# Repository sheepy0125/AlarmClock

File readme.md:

# Alarm Clock

An Alarm Clock created as a school project.

## Hardware (general)

Uses an Arduino Uno (`atmega328p`) as the processor to control:
- 6x 7-segment digits for hours, minutes, and seconds
- 1x character LCD
- 1x snooze button (key switch)
- 1x rotary encoder to adjust time and change other settings (as seen on the LCD)
- 1x piezo buzzer
- 1x real time clock

### Shift registers

Because the Uno only has ~19 available pins, I used serial-in parallel-out buffered shift registers to send one bit at a time and release 8 bits all at once. Each shift register typically needs 2 pins at minimum (one for serial in and one for clock), however, for the seven segment displays I cut that down to 1 per and 1 total for an amortized 7 pins in total where all shift registers share one clock pulse.

## Software

All software is written in Rust with [Rahix's Arduino HAL crate](https://github.com/rahix/avr-hal).

## Design

TODO!!!

## Progress

- [x] Design schematic (done: 2023-09-17)
- [x] Order parts
- [ ] Breadboard / POC (in progress)
- [ ] Design PCB
- [ ] Order PCB parts
- [ ] Finish software (in progress)
- [x] Construct case
- [ ] Integration

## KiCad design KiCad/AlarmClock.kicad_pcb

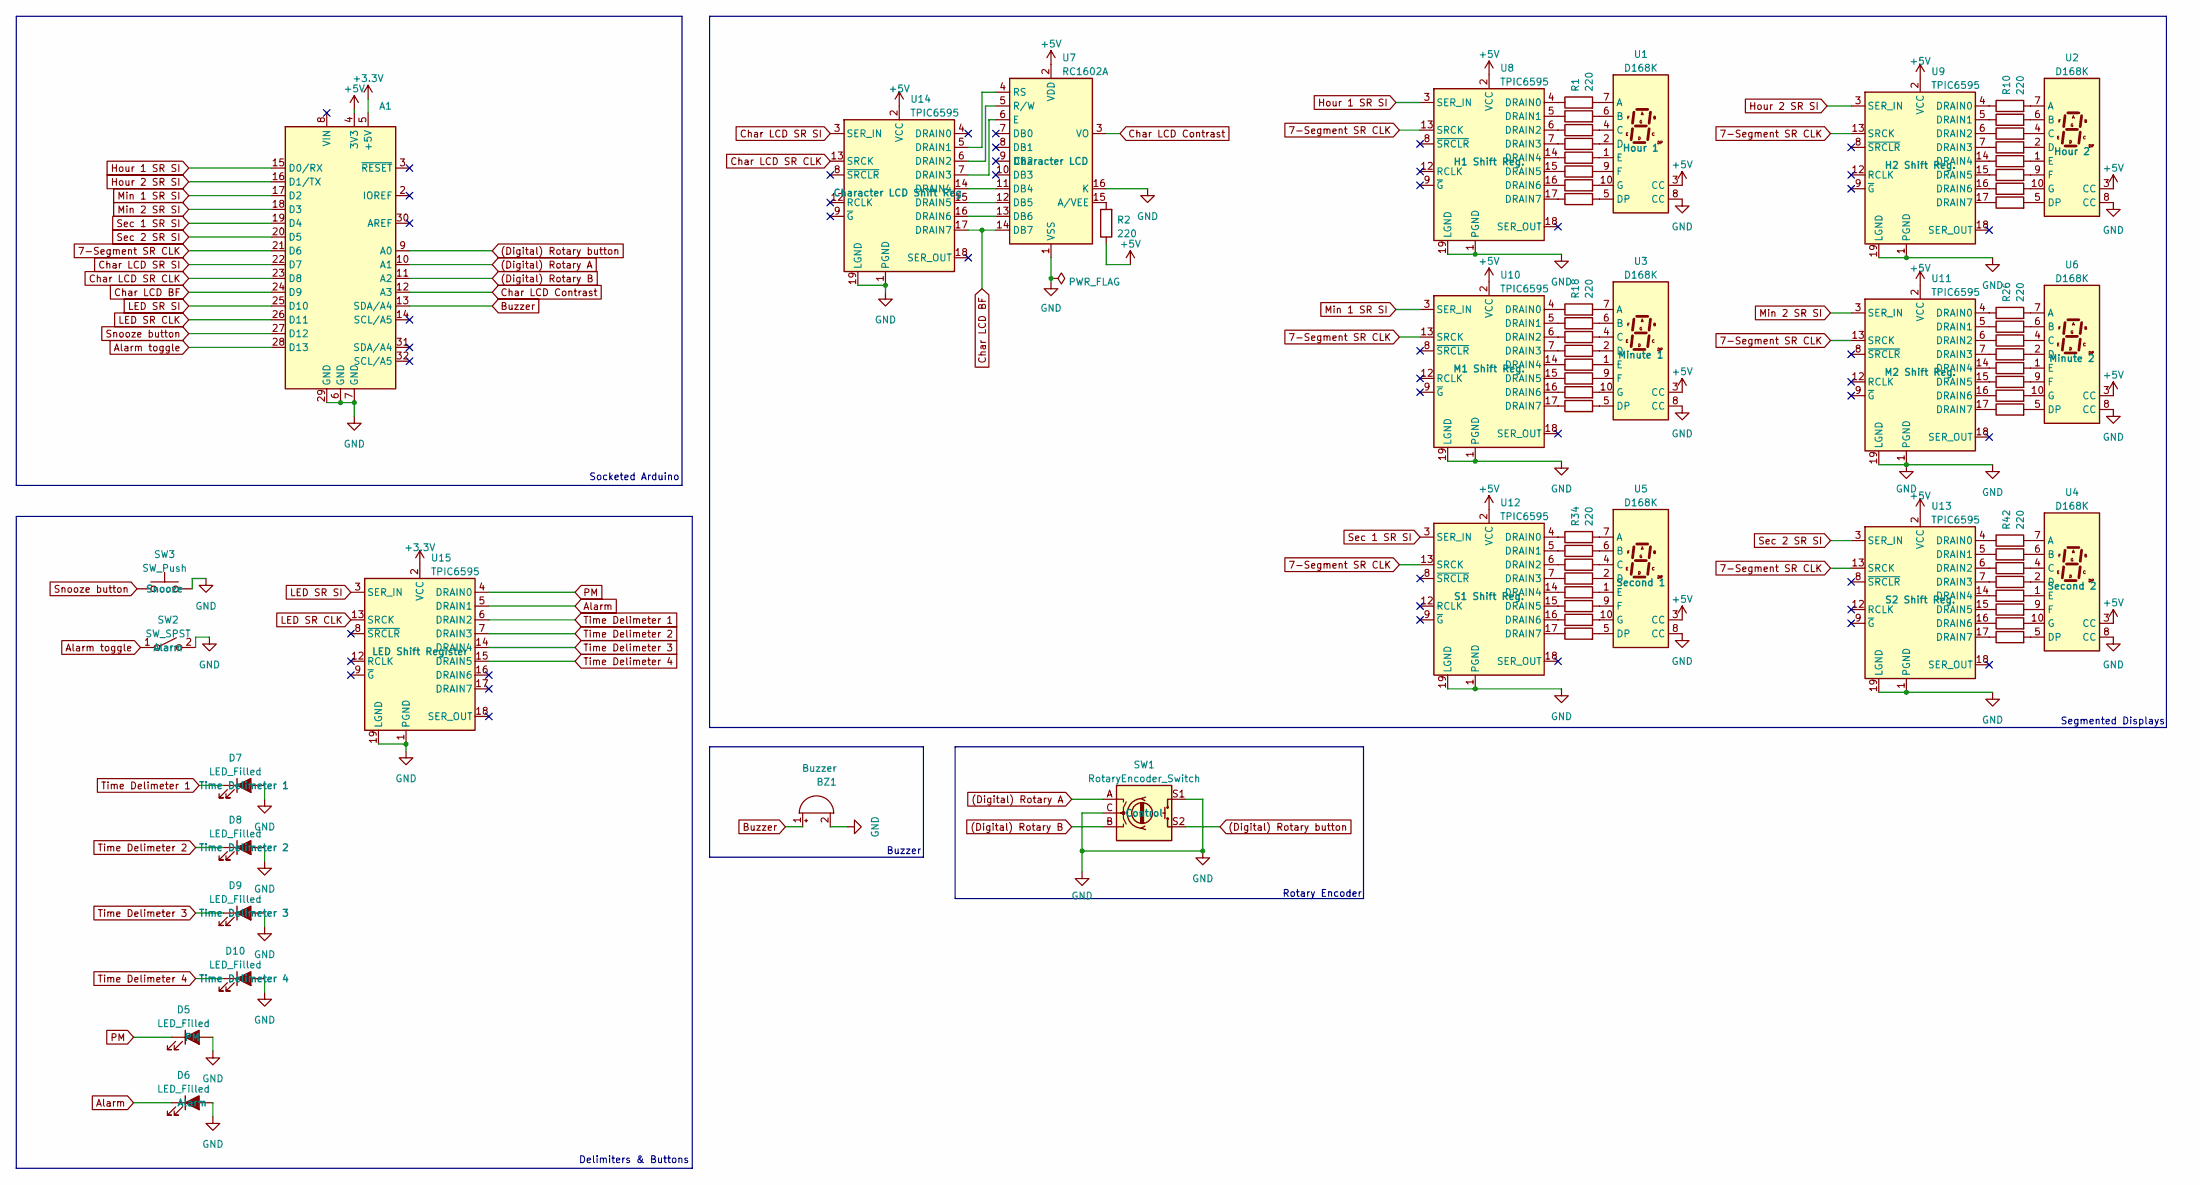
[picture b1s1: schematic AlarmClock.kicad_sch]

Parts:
A1: Arduino_UNO_R3; Arduino_UNO_R3_WithMountingHoles
BZ1: Buzzer; Buzzer_12x9.5RM7.6
D5, D6, D7, D8, D9, D10: LED_Filled; LED_D5.0mm
R1, R2, R3, R4, R5, R6, R7, R8, R9, R10, R11, R12, R13, R14, R15, R16, R17, R18, R19, R20, R21, R22, R23, R24, R25, R26, R27, R28, R29, R30, R31, R32, R33, R34, R35, R36, R37, R38, R39, R40, R41, R42, R43, R44, R45, R46, R47, R48, R49: 220; R_0402_1005Metric
SW1: RotaryEncoder_Switch; RotaryEncoder_Alps_EC11E-Switch_Vertical_H20mm
SW2: SW_SPST; SW_DIP_SPSTx01_Slide_6.7x4.1mm_W8.61mm_P2.54mm_LowProfile
SW3: SW_Push; SW_MX_1u
U1, U2, U3, U4, U5, U6: D168K; D1X8K
U7: RC1602A
U8, U9, U10, U11, U12, U13, U14, U15: TPIC6595; DIP-20_W7.62mm_Socket

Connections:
7-Segment SR CLK: A1.21 (D6), U8.13 (SRCK), U9.13 (SRCK), U10.13 (SRCK), U11.13 (SRCK), U12.13 (SRCK), U13.13 (SRCK)
(Digital) Rotary A: A1.10 (A1), SW1.A
(Digital) Rotary B: A1.11 (A2), SW1.B
(Digital) Rotary button: A1.9 (A0), SW1.S2
+3.3V: A1.5 (+5V), U15.2 (VCC)
Alarm: D6.1 (K), U15.5 (DRAIN1)
Alarm toggle: A1.28 (D13), SW2.1 (A)
Buzzer: A1.13 (SDA/A4), BZ1.1 (-)
Char LCD BF: A1.24 (D9), U7.14 (DB7), U14.17 (DRAIN7)
Char LCD Contrast: A1.12 (A3), U7.3 (VO)
Char LCD SR CLK: A1.23 (D8), U14.13 (SRCK)
Char LCD SR SI: A1.22 (D7), U14.3 (SER_IN)
GND: A1.6 (GND), A1.7 (GND), A1.29 (GND), BZ1.2 (+), D5.2 (A), D6.2 (A), D7.2 (A), D8.2 (A), D9.2 (A), D10.2 (A), SW1.C, SW1.S1, SW2.2 (B), SW3.2, U1.8 (CC), U2.8 (CC), U3.8 (CC), U4.8 (CC), U5.8 (CC), U6.8 (CC), U7.1 (VSS), U7.16 (K), U8.1 (PGND), U8.10 (PGND), U8.11 (PGND), U8.19 (LGND), U8.20 (PGND), U9.1 (PGND), U9.10 (PGND), U9.11 (PGND), U9.19 (LGND), U9.20 (PGND), U10.1 (PGND), U10.10 (PGND), U10.11 (PGND), U10.19 (LGND), U10.20 (PGND), U11.1 (PGND), U11.10 (PGND), U11.11 (PGND), U11.19 (LGND), U11.20 (PGND), U12.1 (PGND), U12.10 (PGND), U12.11 (PGND), U12.19 (LGND), U12.20 (PGND), U13.1 (PGND), U13.10 (PGND), U13.11 (PGND), U13.19 (LGND), U13.20 (PGND), U14.1 (PGND), U14.10 (PGND), U14.11 (PGND), U14.19 (LGND), U14.20 (PGND), U15.1 (PGND), U15.10 (PGND), U15.11 (PGND), U15.19 (LGND), U15.20 (PGND)
Hour 1 SR SI: A1.15 (D0/RX), U8.3 (SER_IN)
Hour 2 SR SI: A1.16 (D1/TX), U9.3 (SER_IN)
LED SR CLK: A1.26 (D11), U15.13 (SRCK)
Min 1 SR SI: A1.17 (D2), U10.3 (SER_IN)
Min 2 SR SI: A1.18 (D3), U11.3 (SER_IN)
unnamed: R1.2, U1.7 (A)
unnamed: R3.2, U1.6 (B)
unnamed: R4.2, U1.4 (C)
unnamed: R5.2, U1.2 (D)
unnamed: R9.2, U1.5 (DP)
unnamed: R6.2, U1.1 (E)
unnamed: R7.2, U1.9 (F)
unnamed: R8.2, U1.10 (G)
unnamed: R10.2, U2.7 (A)
unnamed: R11.2, U2.6 (B)
unnamed: R12.2, U2.4 (C)
unnamed: R13.2, U2.2 (D)
unnamed: R17.2, U2.5 (DP)
unnamed: R14.2, U2.1 (E)
unnamed: R15.2, U2.9 (F)
unnamed: R16.2, U2.10 (G)
unnamed: R18.2, U3.7 (A)
unnamed: R19.2, U3.6 (B)
unnamed: R20.2, U3.4 (C)
unnamed: R21.2, U3.2 (D)
unnamed: R25.2, U3.5 (DP)
unnamed: R22.2, U3.1 (E)
unnamed: R23.2, U3.9 (F)
unnamed: R24.2, U3.10 (G)
unnamed: R42.2, U4.7 (A)
unnamed: R43.2, U4.6 (B)
unnamed: R44.2, U4.4 (C)
unnamed: R45.2, U4.2 (D)
unnamed: R49.2, U4.5 (DP)
unnamed: R46.2, U4.1 (E)
unnamed: R47.2, U4.9 (F)
unnamed: R48.2, U4.10 (G)
unnamed: R34.2, U5.7 (A)
unnamed: R35.2, U5.6 (B)
unnamed: R36.2, U5.4 (C)
unnamed: R37.2, U5.2 (D)
unnamed: R41.2, U5.5 (DP)
unnamed: R38.2, U5.1 (E)
unnamed: R39.2, U5.9 (F)
unnamed: R40.2, U5.10 (G)
unnamed: R26.2, U6.7 (A)
unnamed: R27.2, U6.6 (B)
unnamed: R28.2, U6.4 (C)
unnamed: R29.2, U6.2 (D)
unnamed: R33.2, U6.5 (DP)
unnamed: R30.2, U6.1 (E)
unnamed: R31.2, U6.9 (F)
unnamed: R32.2, U6.10 (G)
unnamed: R1.1, U8.4 (DRAIN0)
unnamed: R3.1, U8.5 (DRAIN1)
unnamed: R4.1, U8.6 (DRAIN2)
unnamed: R5.1, U8.7 (DRAIN3)
unnamed: R6.1, U8.14 (DRAIN4)
unnamed: R7.1, U8.15 (DRAIN5)
unnamed: R8.1, U8.16 (DRAIN6)
unnamed: R9.1, U8.17 (DRAIN7)
unnamed: R10.1, U9.4 (DRAIN0)
unnamed: R11.1, U9.5 (DRAIN1)
unnamed: R12.1, U9.6 (DRAIN2)
unnamed: R13.1, U9.7 (DRAIN3)
unnamed: R14.1, U9.14 (DRAIN4)
unnamed: R15.1, U9.15 (DRAIN5)
unnamed: R16.1, U9.16 (DRAIN6)
unnamed: R17.1, U9.17 (DRAIN7)
unnamed: R18.1, U10.4 (DRAIN0)
unnamed: R19.1, U10.5 (DRAIN1)
unnamed: R20.1, U10.6 (DRAIN2)
unnamed: R21.1, U10.7 (DRAIN3)
unnamed: R22.1, U10.14 (DRAIN4)
unnamed: R23.1, U10.15 (DRAIN5)
unnamed: R24.1, U10.16 (DRAIN6)
unnamed: R25.1, U10.17 (DRAIN7)
unnamed: R26.1, U11.4 (DRAIN0)
unnamed: R27.1, U11.5 (DRAIN1)
unnamed: R28.1, U11.6 (DRAIN2)
unnamed: R29.1, U11.7 (DRAIN3)
unnamed: R30.1, U11.14 (DRAIN4)
unnamed: R31.1, U11.15 (DRAIN5)
unnamed: R32.1, U11.16 (DRAIN6)
unnamed: R33.1, U11.17 (DRAIN7)
unnamed: R34.1, U12.4 (DRAIN0)
unnamed: R35.1, U12.5 (DRAIN1)
unnamed: R36.1, U12.6 (DRAIN2)
unnamed: R37.1, U12.7 (DRAIN3)
unnamed: R38.1, U12.14 (DRAIN4)
unnamed: R39.1, U12.15 (DRAIN5)
unnamed: R40.1, U12.16 (DRAIN6)
unnamed: R41.1, U12.17 (DRAIN7)
unnamed: R42.1, U13.4 (DRAIN0)
unnamed: R43.1, U13.5 (DRAIN1)
unnamed: R44.1, U13.6 (DRAIN2)
unnamed: R45.1, U13.7 (DRAIN3)
unnamed: R46.1, U13.14 (DRAIN4)
unnamed: R47.1, U13.15 (DRAIN5)
unnamed: R48.1, U13.16 (DRAIN6)
unnamed: R49.1, U13.17 (DRAIN7)
unnamed: U7.4 (RS), U14.5 (DRAIN1)
unnamed: U7.5 (R/W), U14.6 (DRAIN2)
unnamed: U7.6 (E), U14.7 (DRAIN3)
unnamed: U7.11 (DB4), U14.14 (DRAIN4)
unnamed: U7.12 (DB5), U14.15 (DRAIN5)
unnamed: U7.13 (DB6), U14.16 (DRAIN6)
PM: D5.1 (K), U15.4 (DRAIN0)
Sec 1 SR SI: A1.19 (D4), U12.3 (SER_IN)
Sec 2 SR SI: A1.20 (D5), U13.3 (SER_IN)
Time Delimeter 1: D7.1 (K), U15.6 (DRAIN2)
Time Delimeter 2: D8.1 (K), U15.7 (DRAIN3)
Time Delimeter 3: D9.1 (K), U15.14 (DRAIN4)
Time Delimeter 4: D10.1 (K), U15.15 (DRAIN5)

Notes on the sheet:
Socketed Arduino
Buzzer
Segmented Displays
Rotary Encoder
Delimiters & Buttons

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
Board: 2 copper layers, 75 parts (1 on the bottom side), 130 nets, no tracks yet.

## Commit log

2023-09-17 Start of PCB design
2023-09-17 Add readme
2023-09-17 Add .gitignore
2023-09-17 Add MIT license
2023-09-18 reformat your questionable schematic, and import components into pcb editor
2023-09-18 fix a very small mistake
2023-09-22 Update schematic to adhere to ERC
2023-10-02 Add interfaces for most peripherals and interrupts
2023-10-10 Interface with most peripherals
